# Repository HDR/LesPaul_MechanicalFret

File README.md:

# Les Paul Mechanical Fret
A replacement Fret board that replaces the rubber membranes with mechancial switches

### Summary
- Compatible with xbox and ps3 Les Paul Guitars
- Compatible with all Kailh 1350 Choc switches, giving you a wide variety of options
- Requires some trimming of the buttons and the neck (Removing some plastic)
- Some trimming of the holes in the pcb may be required if the fit is too tight

### Ordering the PCB
[OSHPark (More, expensive way faster shipping)](https://oshpark.com/shared_projects/sG993t7p)

###### JLCPCB:
Upload gerbers(.zip files) to [JLCPCB](http://jlcpcb.com)

Make sure PCB Thickness is set to 1.6mm

### BOM:

5 of Any Kailh PG1350 Series Choc switch

### Images:

### Switches:

| Color | Type | Product Code | Actuation Force |
|--------------|---------|----------------|-----------------|
| White | Clicky | CPG135001D03 | 50±10gf |
| Brown | Tactile | CPG135001D02 | 50±10gf |
| Red | Linear | CPG135001D01 | 45±10gf |
| Navy | Clicky | CPG135001D03-3 | 70±10gf |
| Jade | Clicky | CPG135001D03-2 | 50±10gf |
| Pale Blue | Clicky | CPG135001D03-1 | 70±10gf |
| Burnt Orange | Tactile | CPG135001D02-1 | 70±10gf |
| Yellow | Linear | CPG135001D01-1 | 70±10gf |

Table by [Deskthority.net](https://deskthority.net/wiki/Kailh_PG1350_series)

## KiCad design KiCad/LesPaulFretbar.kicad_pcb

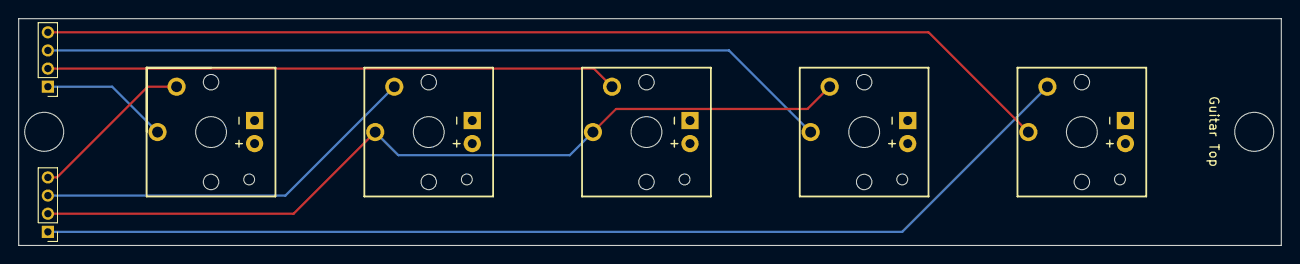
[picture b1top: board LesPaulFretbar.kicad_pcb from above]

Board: 2 copper layers, 139.2 x 25.0 mm, 9 parts (0 on the bottom side), 8 nets.

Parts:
J1, J2: Conn_01x04_Female; PinHeader_1x04_P2.00mm_Vertical
SW1: Green(A); Kailh-PG1350-1.5u
SW2: Red(B); Kailh-PG1350-1.5u
SW3: Yellow(Y); Kailh-PG1350-1.5u
SW4: Blue(X); Kailh-PG1350-1.5u
SW5: Orange(TB); Kailh-PG1350-1.5u
mnt1, mnt2: MountingHole_4.3mm_M4_lespaul

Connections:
unnamed: J1.1, SW1.2
unnamed: J1.2, SW2.2, SW3.1, SW4.1
unnamed: J1.3, SW4.2
unnamed: J1.4, SW5.2
unnamed: J2.1, SW5.1
unnamed: J2.2, SW3.2
unnamed: J2.3, SW2.1
unnamed: J2.4, SW1.1

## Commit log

2019-11-08 Add PCB and readme
2021-01-22 Add kicad files
2022-04-16 Fix spelling
